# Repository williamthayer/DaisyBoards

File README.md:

# DaisyBoards
 A full repo of all the design files for each DaisyBoard

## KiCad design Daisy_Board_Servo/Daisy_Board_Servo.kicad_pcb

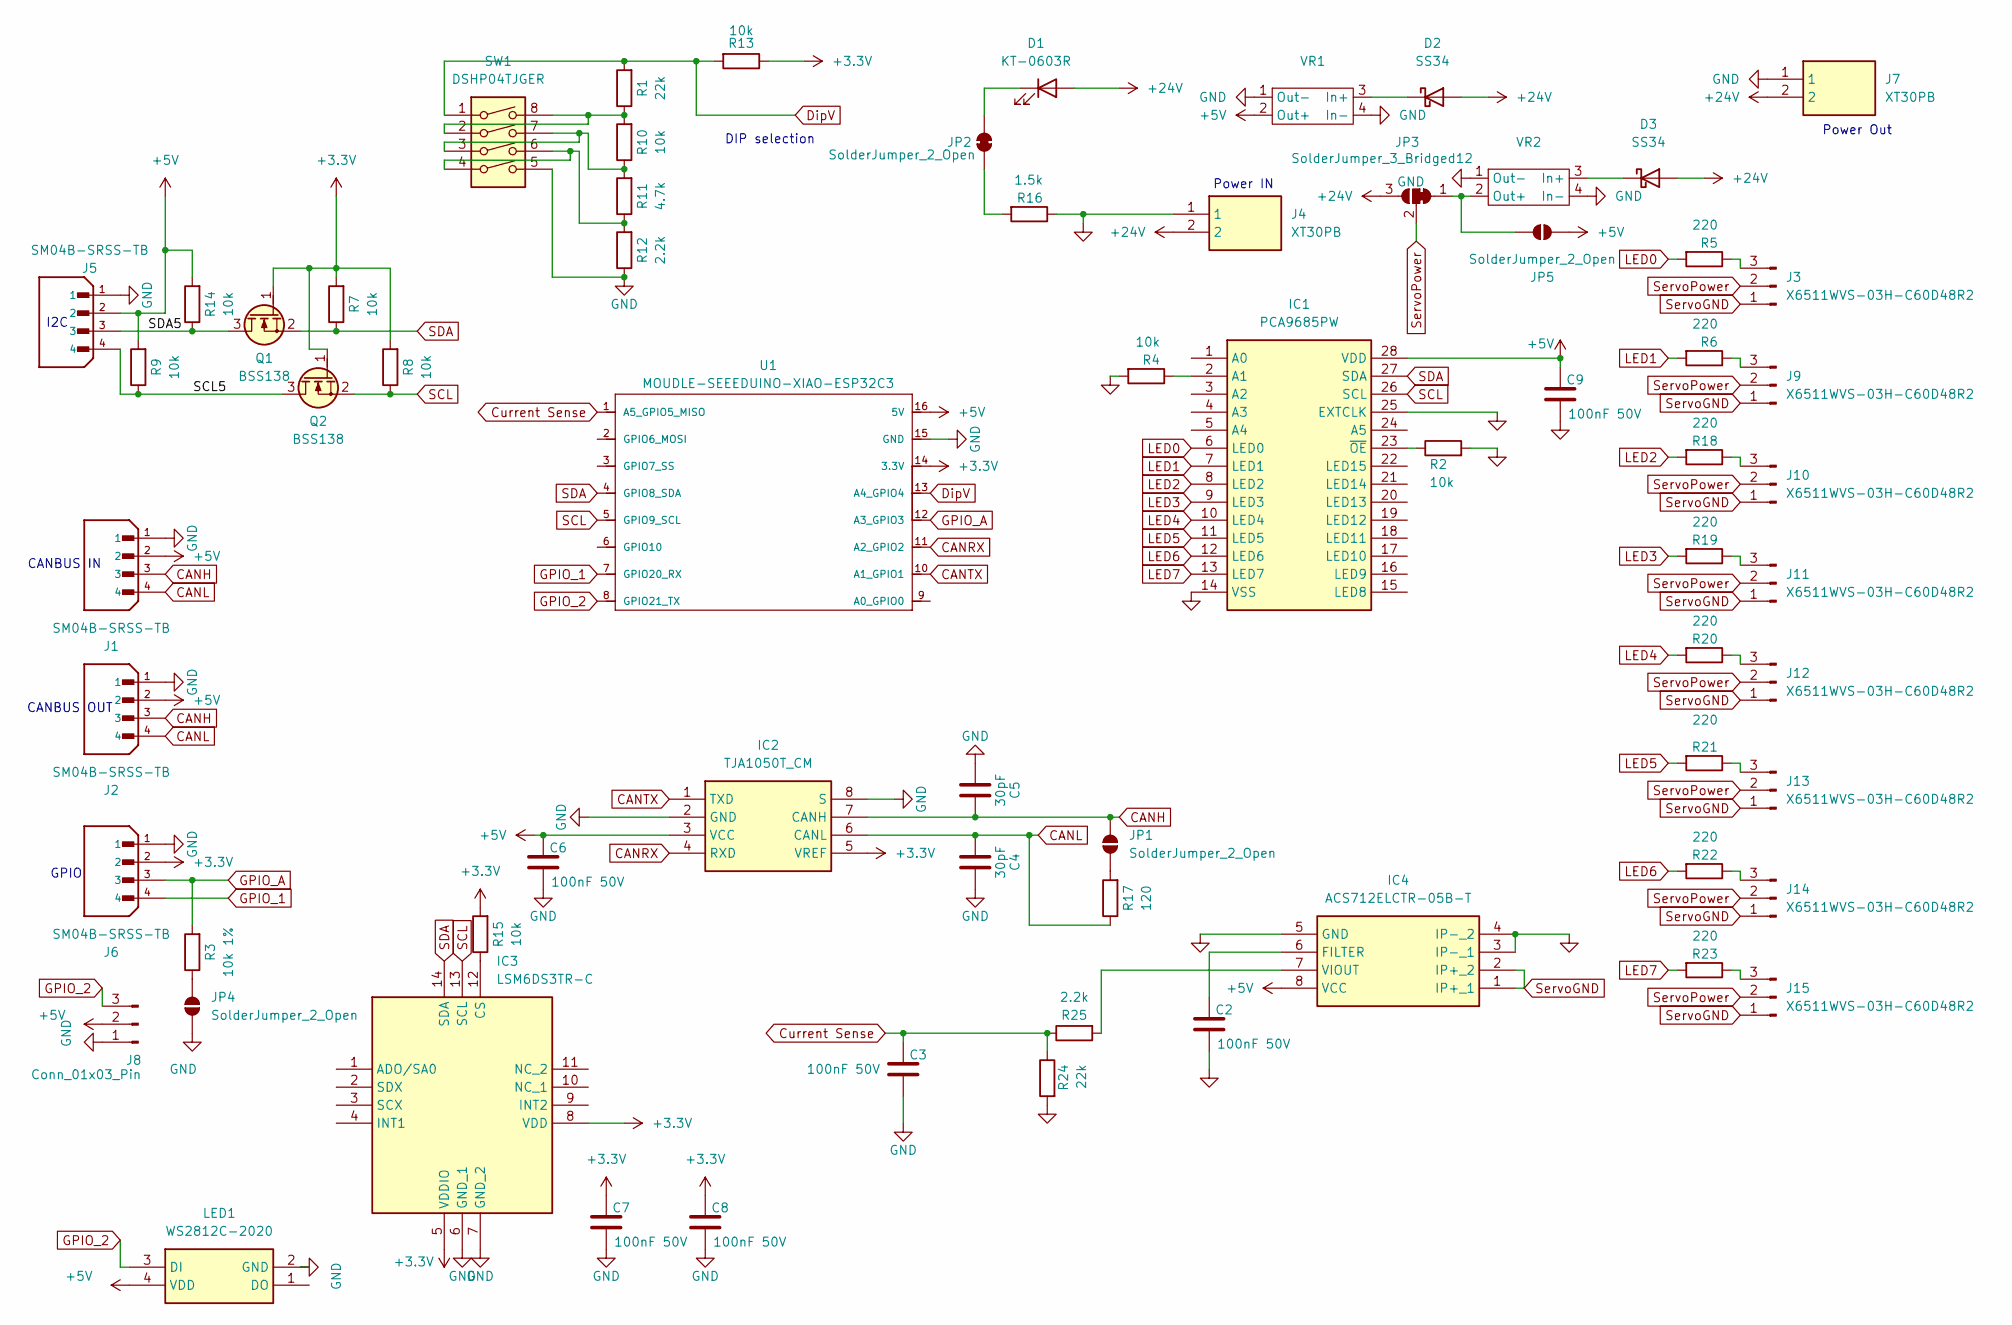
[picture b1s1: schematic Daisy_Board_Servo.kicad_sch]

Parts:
C2, C3, C6, C7, C8, C9: 100nF 50V; C_0402_1005Metric
C4, C5: 30pF; C_0402_1005Metric
D1: KT-0603R; LED_0603_1608Metric
D2, D3: SS34; D_SOD-123
IC1: PCA9685PW; SOP65P640X110-28N; Manufacturer_Part_Number PCA9685PW; Mouser Part Number N/A
IC2: TJA1050T_CM; SOIC127P600X175-8N; Manufacturer_Part_Number TJA1050T/CM; Mouser Part Number N/A
IC3: LSM6DS3TR-C; LSM6DS3USTR; Manufacturer_Part_Number LSM6DS3TR-C; Mouser Part Number 511-LSM6DS3TR-C
IC4: ACS712ELCTR-05B-T; SOIC127P600X175-8N; Manufacturer_Part_Number ACS712ELCTR-05B-T
J1, J2, J5, J6: SM04B-SRSS-TB; JST_SH_SM04B-SRSS-TB_1x04-1MP_P1.00mm_Horizontal
J3, J9, J10, J11, J12, J13, J14, J15: X6511WVS-03H-C60D48R2; PinHeader_1x03_P2.54mm_Vertical_SMD_Pin1Right
J4: XT30PB; Xt30 Horizontal; Manufacturer_Part_Number XT30PB
J7: XT30PB; Manufacturer_Part_Number XT30PB
J8: Conn_01x03_Pin; PinHeader_1x03_P2.54mm_Vertical
JP1, JP4, JP5: SolderJumper_2_Open; SolderJumper-2_P1.3mm_Open_RoundedPad1.0x1.5mm
JP2: SolderJumper_2_Open; Jumper Connected 2 Pin Small
JP3: SolderJumper_3_Bridged12; SolderJumper-3_P1.3mm_Bridged2Bar12_RoundedPad1.0x1.5mm
LED1: WS2812C-2020; WS2812C2020; Manufacturer_Part_Number WS2812C-2020
Q1, Q2: BSS138; SOT-23
R1, R24: 22k; R_0402_1005Metric
R2, R4, R7, R8, R9, R10, R13, R14, R15: 10k; R_0402_1005Metric
R3: 10k 1%; R_0402_1005Metric
R5, R6, R18, R19, R20, R21, R22, R23: 220; R_0402_1005Metric
R11: 4.7k; R_0402_1005Metric
R12, R25: 2.2k; R_0402_1005Metric
R16: 1.5k; R_0402_1005Metric
R17: 120; R_0402_1005Metric
SW1: DSHP04TJGER; SW_DIP_SPSTx04_Slide_Copal_CHS-04A_W5.08mm_P1.27mm_JPin
U1: MOUDLE-SEEEDUINO-XIAO-ESP32C3; MOUDLE14P-SMD-2.54-21X17.8MM
VR1, VR2: EY9 reg board

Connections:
+3.3V: C7.1, C8.1, IC2.5 (VREF), IC3.5 (VDDIO), IC3.8 (VDD), J6.2, Q1.1 (G), Q2.1 (G), R7.2, R8.2, R13.1, R15.2, U1.14 (3.3V)
+5V: C6.1, C9.1, IC1.28 (VDD), IC2.3 (VCC), IC4.8 (VCC), J1.2, J2.2, J5.2, J8.2, JP5.2 (B), LED1.4 (VDD), R9.2, R14.2, U1.16 (5V), VR1.2 (Out+)
+24V: D1.2 (A), D2.2 (A), D3.2 (A), J4.2, J7.2, JP3.3 (B)
/SCL5: J5.4, Q2.3 (D), R9.1
/SDA5: J5.3, Q1.3 (D), R14.1
CANH: C5.1, IC2.7 (CANH), J1.3, J2.3, JP1.2 (B)
CANL: C4.2, IC2.6 (CANL), J1.4, J2.4, R17.1
CANRX: IC2.4 (RXD), U1.11 (A2_GPIO2)
CANTX: IC2.1 (TXD), U1.10 (A1_GPIO1)
Current Sense: C3.1, R24.1, R25.1, U1.1 (A5_GPIO5_MISO)
DipV: R1.2, R13.2, SW1.1, U1.13 (A4_GPIO4)
GND: C2.2, C3.2, C4.1, C5.2, C6.2, C7.2, C8.2, C9.2, IC1.14 (VSS), IC1.25 (EXTCLK), IC2.2 (GND), IC2.8 (S), IC3.6 (GND_1), IC3.7 (GND_2), IC4.3 (IP-_1), IC4.4 (IP-_2), IC4.5 (GND), J1.1, J2.1, J4.1, J5.1, J6.1, J7.1, J8.1, JP4.1 (A), LED1.2 (GND), R2.2, R4.2, R12.1, R16.1, R24.2, SW1.5, U1.15 (GND), VR1.1 (Out-), VR1.4 (In-), VR2.1 (Out-), VR2.4 (In-)
GPIO_1: J6.4, U1.7 (GPIO20_RX)
GPIO_2: J8.3, LED1.3 (DI), U1.8 (GPIO21_TX)
GPIO_A: J6.3, R3.2, U1.12 (A3_GPIO3)
LED0: IC1.6 (LED0), R5.2
LED1: IC1.7 (LED1), R6.2
LED2: IC1.8 (LED2), R18.2
LED3: IC1.9 (LED3), R19.2
LED4: IC1.10 (LED4), R20.2
LED5: IC1.11 (LED5), R21.2
LED6: IC1.12 (LED6), R22.2
LED7: IC1.13 (LED7), R23.2
unnamed: D1.1 (K), JP2.2 (B)
unnamed: D2.1 (K), VR1.3 (In+)
unnamed: D3.1 (K), VR2.3 (In+)
unnamed: IC1.2 (A1), R4.1
unnamed: IC1.23 (~OE), R2.1
unnamed: IC3.12 (CS), R15.1
unnamed: C2.1, IC4.6 (FILTER)
unnamed: IC4.7 (VIOUT), R25.2
unnamed: J3.3, R5.1
unnamed: J9.3, R6.1
unnamed: J10.3, R18.1
unnamed: J11.3, R19.1
unnamed: J12.3, R20.1
unnamed: J13.3, R21.1
unnamed: J14.3, R22.1
unnamed: J15.3, R23.1
unnamed: JP1.1 (A), R17.2
unnamed: JP2.1 (A), R16.2
unnamed: JP3.1 (A), JP5.1 (A), VR2.2 (Out+)
unnamed: JP4.2 (B), R3.1
unnamed: R1.1, R10.2, SW1.2, SW1.8
unnamed: R10.1, R11.2, SW1.3, SW1.7
unnamed: R11.1, R12.2, SW1.4, SW1.6
SCL: IC1.26 (SCL), IC3.13 (SCL), Q2.2 (S), R8.1, U1.5 (GPIO9_SCL)
SDA: IC1.27 (SDA), IC3.14 (SDA), Q1.2 (S), R7.1, U1.4 (GPIO8_SDA)
ServoGND: IC4.1 (IP+_1), IC4.2 (IP+_2), J3.1, J9.1, J10.1, J11.1, J12.1, J13.1, J14.1, J15.1
ServoPower: J3.2, J9.2, J10.2, J11.2, J12.2, J13.2, J14.2, J15.2, JP3.2 (C)

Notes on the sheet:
CANBUS OUT
GPIO
Power Out
CANBUS IN
Power IN
DIP selection
I2C

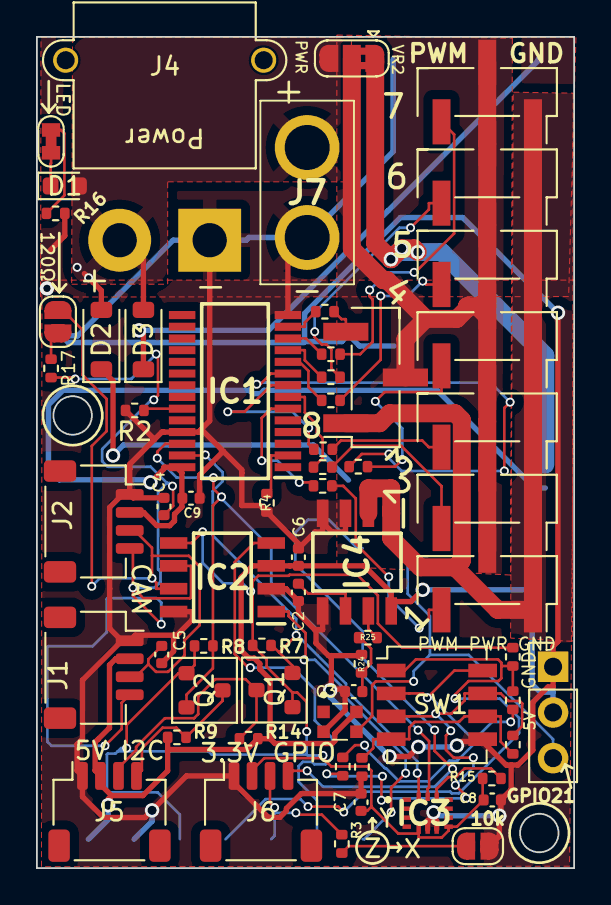
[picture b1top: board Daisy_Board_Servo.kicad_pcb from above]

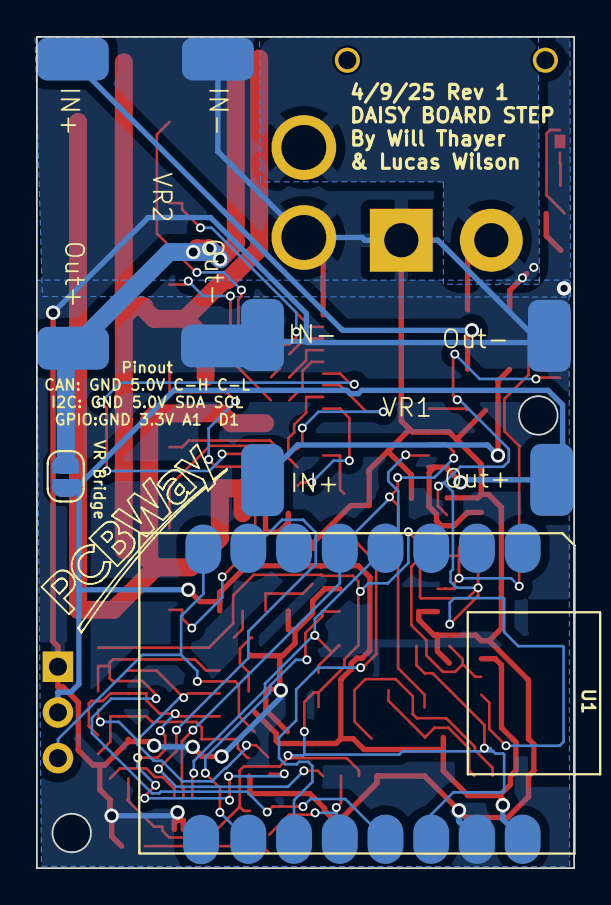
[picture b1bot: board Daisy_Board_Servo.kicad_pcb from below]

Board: 2 copper layers, 29.8 x 46.2 mm, 67 parts (4 on the bottom side), 50 nets.

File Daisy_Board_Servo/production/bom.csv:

Designator,Footprint,Quantity,Value,LCSC Part #
C1,0402,1,22nF 50V,
"C10, C2, C3, C6, C7, C8, C9",0402,7,100nF 50V,
"C4, C5",0402,2,30pF,
D1,0603,1,KT-0603R,
D2,D_SOD-123,1,SS34,
IC2,SOIC127P600X175-8N,1,TJA1050T_CM,
IC3,LSM6DS3USTR,1,LSM6DS3TR-C,
IC4,QFN50P500X500X90-29N,1,TMC2209-LA,
"J1, J2, J5, J6",JST_SH_SM04B-SRSS-TB_1x04-1MP_P1.00mm_Horizontal,4,SM04B-SRSS-TB,
"Q1, Q2",SOT-23,2,BSS138,
R1,0402,1,22k,
"R10, R13, R14, R15, R3, R7, R8, R9",0402,8,10k,
R11,0402,1,4.7k,
R12,0402,1,2.2k,
R16,0402,1,1.5k,
R17,0402,1,120,
R2,0402,1,1k,
SW1,SW_DIP_SPSTx04_Slide_Copal_CHS-04A_W5.08mm_P1.27mm_JPin,1,DSHP04TJGER,

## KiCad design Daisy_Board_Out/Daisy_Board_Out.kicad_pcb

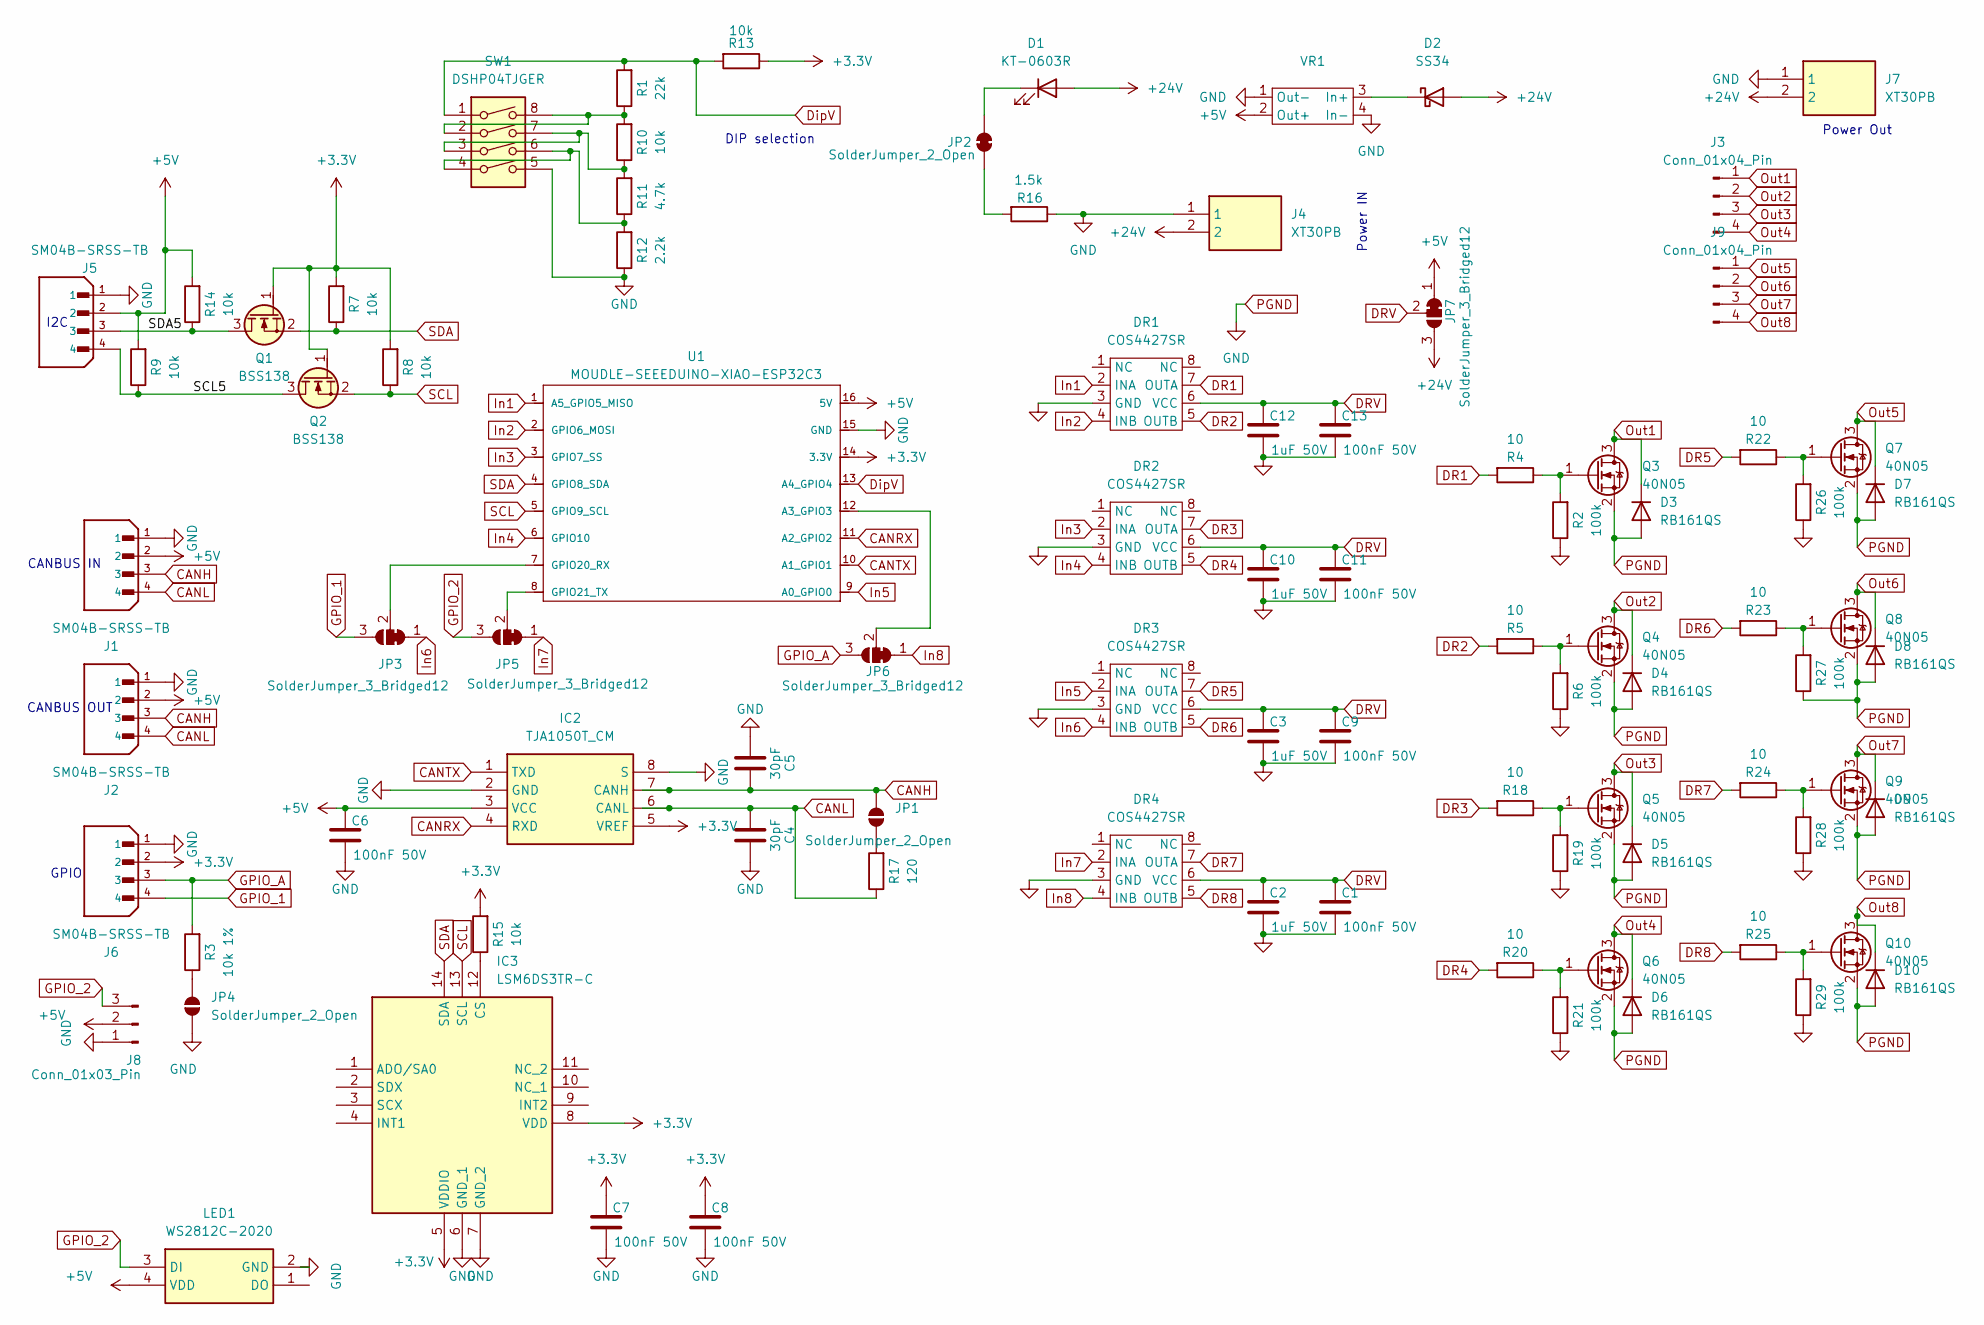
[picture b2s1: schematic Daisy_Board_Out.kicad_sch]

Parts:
C1, C6, C7, C8, C9, C11, C13: 100nF 50V; C_0402_1005Metric
C2, C3, C10, C12: 1uF 50V; C_0402_1005Metric
C4, C5: 30pF; C_0402_1005Metric
D1: KT-0603R; LED_0603_1608Metric
D2: SS34; D_SOD-123
D3, D4, D5, D6, D7, D8, D9, D10: RB161QS; D_0402_1005Metric
DR1, DR2, DR3, DR4: COS4427SR; SOP-8_3.76x4.96mm_P1.27mm
IC2: TJA1050T_CM; SOIC127P600X175-8N; Manufacturer_Part_Number TJA1050T/CM; Mouser Part Number N/A
IC3: LSM6DS3TR-C; LSM6DS3USTR; Manufacturer_Part_Number LSM6DS3TR-C; Mouser Part Number 511-LSM6DS3TR-C
J1, J2, J5, J6: SM04B-SRSS-TB; JST_SH_SM04B-SRSS-TB_1x04-1MP_P1.00mm_Horizontal
J3, J9: Conn_01x04_Pin; TerminalBlock_Xinya_XY308-2.54-4P_1x04_P2.54mm_Horizontal
J4: XT30PB; Xt30 Horizontal; Manufacturer_Part_Number XT30PB
J7: XT30PB; Manufacturer_Part_Number XT30PB
J8: Conn_01x03_Pin; PinHeader_1x03_P2.54mm_Vertical
JP1, JP4: SolderJumper_2_Open; SolderJumper-2_P1.3mm_Open_RoundedPad1.0x1.5mm
JP2: SolderJumper_2_Open; Jumper Connected 2 Pin Small
JP3, JP5, JP6, JP7: SolderJumper_3_Bridged12; SolderJumper-3_P1.3mm_Bridged12_RoundedPad1.0x1.5mm
LED1: WS2812C-2020; WS2812C2020; Manufacturer_Part_Number WS2812C-2020
Q1, Q2: BSS138; SOT-23
Q3, Q4, Q5, Q6, Q7, Q8, Q9, Q10: 40N05; SOT-23-3
R1: 22k; R_0402_1005Metric
R2, R6, R19, R21, R26, R27, R28, R29: 100k; R_0402_1005Metric
R3: 10k 1%; R_0402_1005Metric
R4, R5, R18, R20, R22, R23, R24, R25: 10; R_0603_1608Metric
R7, R8, R9, R10, R13, R14, R15: 10k; R_0402_1005Metric
R11: 4.7k; R_0402_1005Metric
R12: 2.2k; R_0402_1005Metric
R16: 1.5k; R_0402_1005Metric
R17: 120; R_0402_1005Metric
SW1: DSHP04TJGER; SW_DIP_SPSTx04_Slide_Copal_CHS-04A_W5.08mm_P1.27mm_JPin
U1: MOUDLE-SEEEDUINO-XIAO-ESP32C3; MOUDLE14P-SMD-2.54-21X17.8MM
VR1: EY9 reg board

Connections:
+3.3V: C7.1, C8.1, IC2.5 (VREF), IC3.5 (VDDIO), IC3.8 (VDD), J6.2, Q1.1 (G), Q2.1 (G), R7.2, R8.2, R13.1, R15.2, U1.14 (3.3V)
+5V: C6.1, IC2.3 (VCC), J1.2, J2.2, J5.2, J8.2, JP7.1 (A), LED1.4 (VDD), R9.2, R14.2, U1.16 (5V), VR1.2 (Out+)
+24V: D1.2 (A), D2.2 (A), J4.2, J7.2, JP7.3 (B)
/SCL5: J5.4, Q2.3 (D), R9.1
/SDA5: J5.3, Q1.3 (D), R14.1
CANH: C5.1, IC2.7 (CANH), J1.3, J2.3, JP1.2 (B)
CANL: C4.2, IC2.6 (CANL), J1.4, J2.4, R17.1
CANRX: IC2.4 (RXD), U1.11 (A2_GPIO2)
CANTX: IC2.1 (TXD), U1.10 (A1_GPIO1)
DR1: DR1.7 (OUTA), R4.2
DR2: DR1.5 (OUTB), R5.2
DR3: DR2.7 (OUTA), R18.2
DR4: DR2.5 (OUTB), R20.2
DR5: DR3.7 (OUTA), R22.2
DR6: DR3.5 (OUTB), R23.2
DR7: DR4.7 (OUTA), R24.2
DR8: DR4.5 (OUTB), R25.2
DRV: C1.1, C2.1, C3.1, C9.1, C10.1, C11.1, C12.1, C13.1, DR1.6 (VCC), DR2.6 (VCC), DR3.6 (VCC), DR4.6 (VCC), JP7.2 (C)
DipV: R1.2, R13.2, SW1.1, U1.13 (A4_GPIO4)
GPIO_1: J6.4, JP3.3 (B)
GPIO_2: J8.3, JP5.3 (B), LED1.3 (DI)
GPIO_A: J6.3, JP6.3 (B), R3.2
In1: DR1.2 (INA), U1.1 (A5_GPIO5_MISO)
In2: DR1.4 (INB), U1.2 (GPIO6_MOSI)
In3: DR2.2 (INA), U1.3 (GPIO7_SS)
In4: DR2.4 (INB), U1.6 (GPIO10)
In5: DR3.2 (INA), U1.9 (A0_GPIO0)
In6: DR3.4 (INB), JP3.1 (A)
In7: DR4.2 (INA), JP5.1 (A)
In8: DR4.4 (INB), JP6.1 (A)
unnamed: D1.1 (K), JP2.2 (B)
unnamed: D2.1 (K), VR1.3 (In+)
unnamed: IC3.12 (CS), R15.1
unnamed: JP1.1 (A), R17.2
unnamed: JP2.1 (A), R16.2
unnamed: JP3.2 (C), U1.7 (GPIO20_RX)
unnamed: JP4.2 (B), R3.1
unnamed: JP5.2 (C), U1.8 (GPIO21_TX)
unnamed: JP6.2 (C), U1.12 (A3_GPIO3)
unnamed: Q3.1 (G), R2.2, R4.1
unnamed: Q4.1 (G), R5.1, R6.2
unnamed: Q5.1 (G), R18.1, R19.2
unnamed: Q6.1 (G), R20.1, R21.2
unnamed: Q7.1 (G), R22.1, R26.2
unnamed: Q8.1 (G), R23.1, R27.2
unnamed: Q9.1 (G), R24.1, R28.2
unnamed: Q10.1 (G), R25.1, R29.2
unnamed: R1.1, R10.2, SW1.2, SW1.8
unnamed: R10.1, R11.2, SW1.3, SW1.7
unnamed: R11.1, R12.2, SW1.4, SW1.6
Out1: D3.1 (K), J3.1, Q3.3 (D)
Out2: D4.1 (K), J3.2, Q4.3 (D)
Out3: D5.1 (K), J3.3, Q5.3 (D)
Out4: D6.1 (K), J3.4, Q6.3 (D)
Out5: D7.1 (K), J9.1, Q7.3 (D)
Out6: D8.1 (K), J9.2, Q8.3 (D)
Out7: D9.1 (K), J9.3, Q9.3 (D)
Out8: D10.1 (K), J9.4, Q10.3 (D)
PGND: C1.2, C2.2, C3.2, C4.1, C5.2, C6.2, C7.2, C8.2, C9.2, C10.2, C11.2, C12.2, C13.2, D3.2 (A), D4.2 (A), D5.2 (A), D6.2 (A), D7.2 (A), D8.2 (A), D9.2 (A), D10.2 (A), DR1.3 (GND), DR2.3 (GND), DR3.3 (GND), DR4.3 (GND), IC2.2 (GND), IC2.8 (S), IC3.6 (GND_1), IC3.7 (GND_2), J1.1, J2.1, J4.1, J5.1, J6.1, J7.1, J8.1, JP4.1 (A), LED1.2 (GND), Q3.2 (S), Q4.2 (S), Q5.2 (S), Q6.2 (S), Q7.2 (S), Q8.2 (S), Q9.2 (S), Q10.2 (S), R2.1, R6.1, R12.1, R16.1, R19.1, R21.1, R26.1, R27.1, R28.1, R29.1, SW1.5, U1.15 (GND), VR1.1 (Out-), VR1.4 (In-)
SCL: IC3.13 (SCL), Q2.2 (S), R8.1, U1.5 (GPIO9_SCL)
SDA: IC3.14 (SDA), Q1.2 (S), R7.1, U1.4 (GPIO8_SDA)

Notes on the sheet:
CANBUS OUT
GPIO
Power Out
CANBUS IN
Power IN
DIP selection
I2C

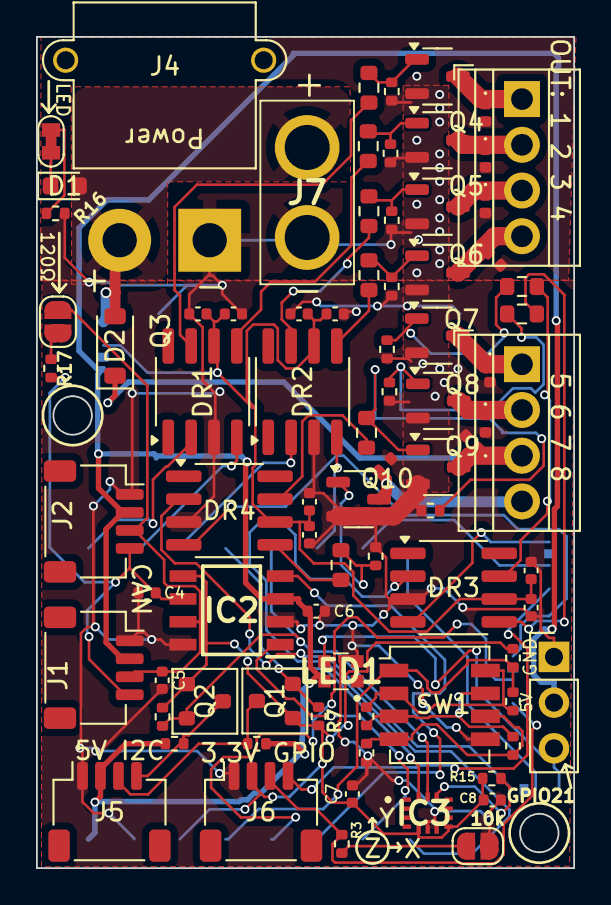
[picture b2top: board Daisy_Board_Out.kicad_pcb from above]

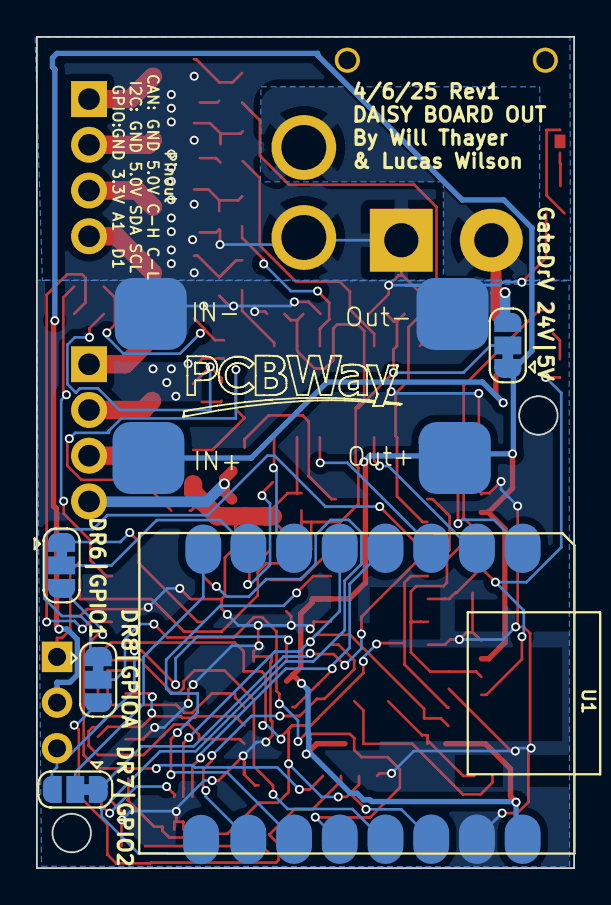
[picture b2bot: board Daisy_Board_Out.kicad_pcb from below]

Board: 2 copper layers, 29.8 x 46.2 mm, 88 parts (6 on the bottom side), 61 nets.

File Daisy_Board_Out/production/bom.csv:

Designator,Footprint,Quantity,Value,LCSC Part #
"C1, C11, C13, C6, C7, C8, C9",0402,7,100nF 50V,
"C10, C12, C2, C3",0402,4,1uF 50V,
"C4, C5",0402,2,30pF,
D1,0603,1,KT-0603R,
D2,D_SOD-123,1,SS34,
"DR1, DR2, DR3, DR4",SOP-8_3.76x4.96mm_P1.27mm,4,COS4427SR,
IC2,SOIC127P600X175-8N,1,TJA1050T_CM,
IC3,LSM6DS3USTR,1,LSM6DS3TR-C,
"J1, J2, J5, J6",JST_SH_SM04B-SRSS-TB_1x04-1MP_P1.00mm_Horizontal,4,SM04B-SRSS-TB,
"J3, J9",TerminalBlock_Xinya_XY308-2.54-4P_1x04_P2.54mm_Horizontal,2,Conn_01x04_Pin,
J8,PinHeader_1x03_P2.54mm_Vertical,1,Conn_01x03_Pin,
LED1,WS2812C2020,1,WS2812C-2020,
"Q1, Q2",SOT-23,2,BSS138,
"Q10, Q3, Q4, Q5, Q6, Q7, Q8, Q9",SOT-23-3,8,DO3012AA,
R1,0402,1,22k,
"R10, R13, R14, R15, R7, R8, R9",0402,7,10k,
R11,0402,1,4.7k,
R12,0402,1,2.2k,
R16,0402,1,1.5k,
R17,0402,1,120,
"R18, R20, R22, R23, R24, R25, R4, R5",0603,8,10,
"R19, R2, R21, R26, R27, R28, R29, R6",0402,8,100k,
R3,0402,1,10k 1%,
SW1,SW_DIP_SPSTx04_Slide_Copal_CHS-04A_W5.08mm_P1.27mm_JPin,1,DSHP04TJGER,
U1,ESP32-C3 16 Pin Super Mini,1,MOUDLE-SEEEDUINO-XIAO-ESP32C3,

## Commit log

2025-04-01 Uploading All current files
2025-04-01 Added Panelized Files
2025-04-01 File Clean up
2025-04-05 panel
2025-04-07 DaisyBoardOut
2025-04-08 Minor Updates
2025-04-08 Minor
2025-04-08 Servo Board
2025-04-11 Done Servo
2025-04-15 Panel Kit updates
2025-04-15 panel updates for lower QTY parts
2025-05-08 New Production Files
